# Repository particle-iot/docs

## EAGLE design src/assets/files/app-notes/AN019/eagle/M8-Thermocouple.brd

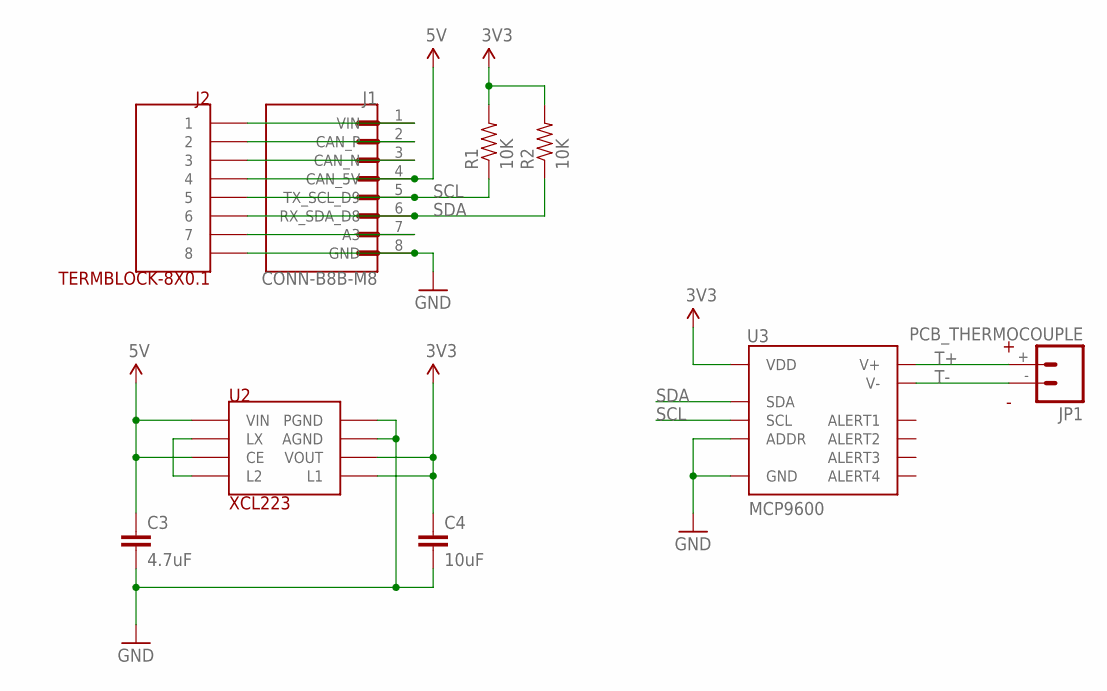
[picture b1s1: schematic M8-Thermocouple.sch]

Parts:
C3: 4.7uF; 0603-CAP
C4: 10uF; 0603-CAP
J1: CONN-B8B-M8; JST_B8B-PH-SM4-TB(LF)(SN)
J2: TERMBLOCK-8X0.1
JP1: PCB_THERMOCOUPLE; PCC-SMP
R1, R2: 10K; 0603-RES
U2: XCL223; REG-XCL223-LESS-CREAM
U3: MCP9600; MQFN-20

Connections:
3V3: C4.1, R1.2, R2.2, U2.3 (VOUT), U2.7 (L1), U3.8 (VDD)
5V: C3.1, J1.4 (CAN_5V), J2.P$4 (4), U2.4 (CE), U2.6 (VIN)
A3: J1.7 (A3), J2.P$7 (7)
CAN_N: J1.3 (CAN_N), J2.P$3 (3)
CAN_P: J1.2 (CAN_P), J2.P$2 (2)
GND: C3.2, C4.2, J1.8 (GND), J2.P$8 (8), U2.1 (PGND), U2.2 (AGND), U3.1 (GND), U3.3 (GND), U3.5 (GND), U3.6 (GND), U3.7 (GND), U3.9 (GND), U3.10 (GND), U3.13 (GND), U3.16 (ADDR), U3.17 (GND), U3.18 (GND), U3.21 (GND)
LX: U2.5 (LX), U2.8 (L2)
SCL: J1.5 (TX_SCL_D9), J2.P$5 (5), R1.1, U3.19 (SCL)
SDA: J1.6 (RX_SDA_D8), J2.P$6 (6), R2.1, U3.20 (SDA)
T+: JP1.+, U3.2 (V+)
T-: JP1.-, U3.4 (V-)
VIN: J1.1 (VIN), J2.P$1 (1)

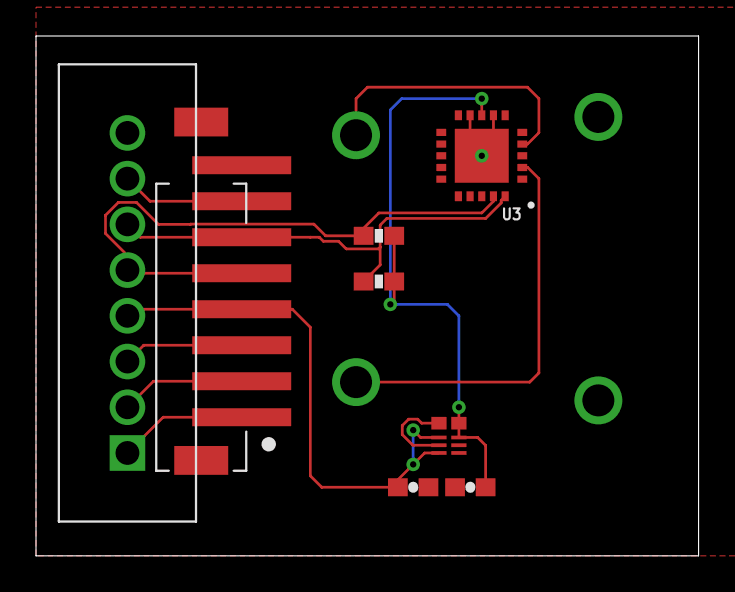
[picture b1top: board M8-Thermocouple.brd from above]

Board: 2 copper layers, 36.8 x 28.9 mm, 9 parts (1 on the bottom side), 12 nets.

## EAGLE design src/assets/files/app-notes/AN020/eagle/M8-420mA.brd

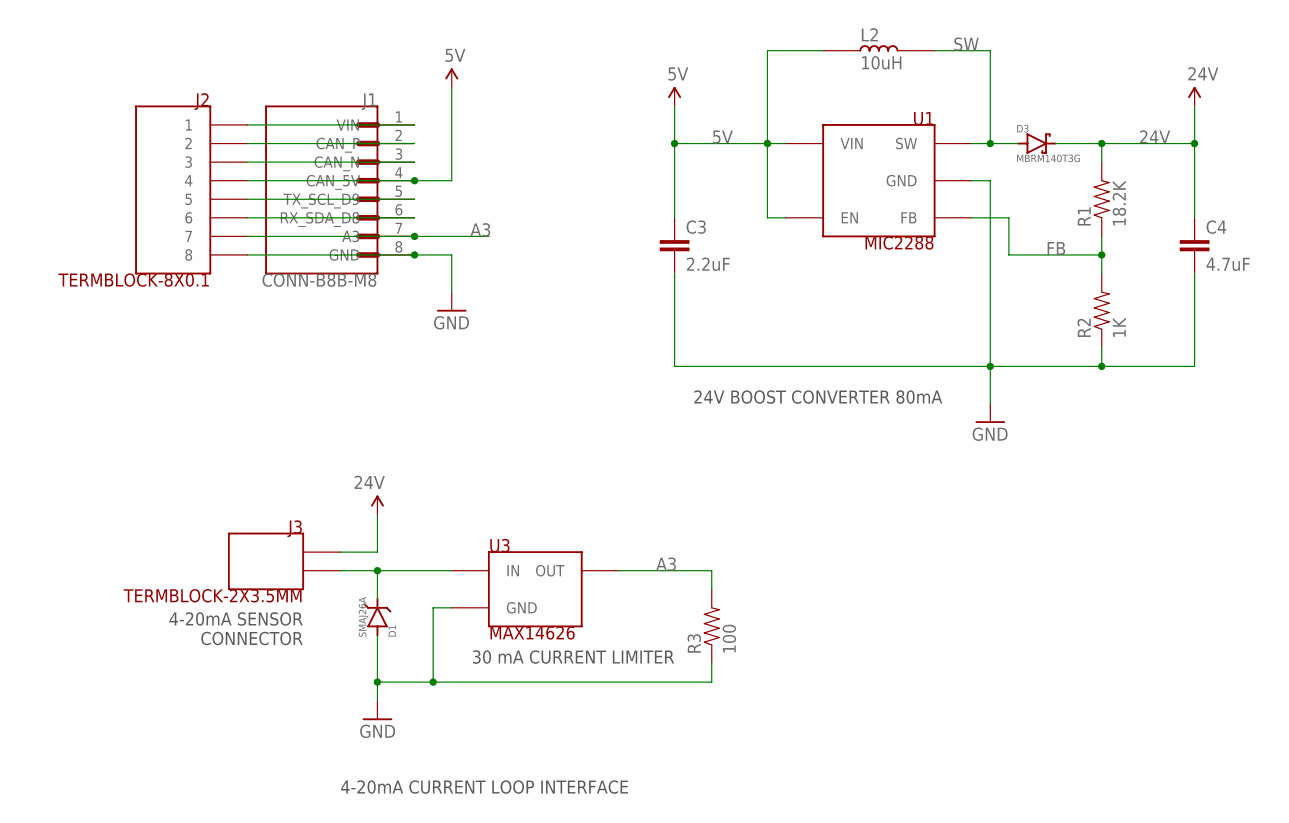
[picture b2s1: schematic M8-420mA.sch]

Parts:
C3: 2.2uF; 0603-CAP
C4: 4.7uF; 0805
D1: SMAJ26A; DO-214AC-LITTELFUSE
D3: MBRM140T3G
J1: CONN-B8B-M8; JST_B8B-PH-SM4-TB(LF)(SN)
J2: TERMBLOCK-8X0.1
J3: TERMBLOCK-2X3.5MM
L2: 10uH; BOURNS-INDUCTOR-3X3
R1: 18.2K; 0603-RES
R2: 1K; 0603-RES
R3: 100; 0603-RES
U1: MIC2288; TSOT23-5-MICROCHIP
U3: MAX14626; 6-TDFN-MAXIM

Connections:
5V: C3.1, J1.4 (CAN_5V), J2.P$4 (4), L2.1, U1.4 (EN), U1.5 (VIN)
24V: C4.1, D3.1 (CATHODE), J3.1, R1.2
A3: J1.7 (A3), J2.P$7 (7), R3.2, U3.6 (OUT)
CAN_N: J1.3 (CAN_N), J2.P$3 (3)
CAN_P: J1.2 (CAN_P), J2.P$2 (2)
FB: R1.1, R2.2, U1.3 (FB)
GND: C3.2, C4.2, D1.A (ANODE), J1.8 (GND), J2.P$8 (8), R2.1, R3.1, U1.2 (GND), U3.2 (GND), U3.3 (GND), U3.4 (GND), U3.5 (GND), U3.EP (GND)
unnamed: J1.5 (TX_SCL_D9), J2.P$5 (5)
SDA: J1.6 (RX_SDA_D8), J2.P$6 (6)
SEN1: D1.C (CATHODE), J3.2, U3.1 (IN)
SW: D3.2 (ANODE), L2.2, U1.1 (SW)
VIN: J1.1 (VIN), J2.P$1 (1)

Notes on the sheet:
24V BOOST CONVERTER 80mA
30 mA CURRENT LIMITER
4-20mA SENSOR CONNECTOR
4-20mA CURRENT LOOP INTERFACE

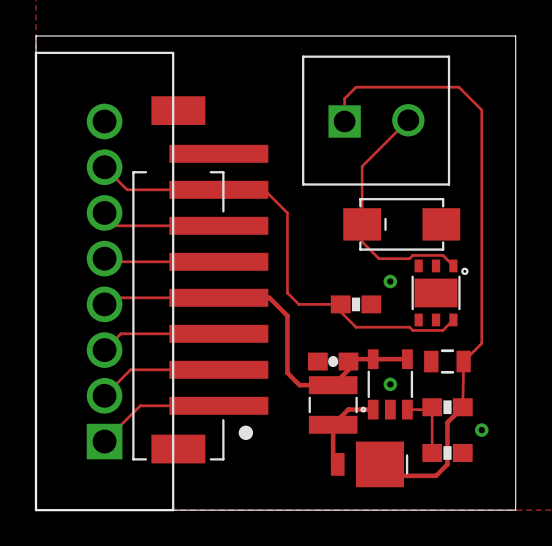
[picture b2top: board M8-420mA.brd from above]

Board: 2 copper layers, 26.6 x 26.3 mm, 13 parts (0 on the bottom side), 12 nets.

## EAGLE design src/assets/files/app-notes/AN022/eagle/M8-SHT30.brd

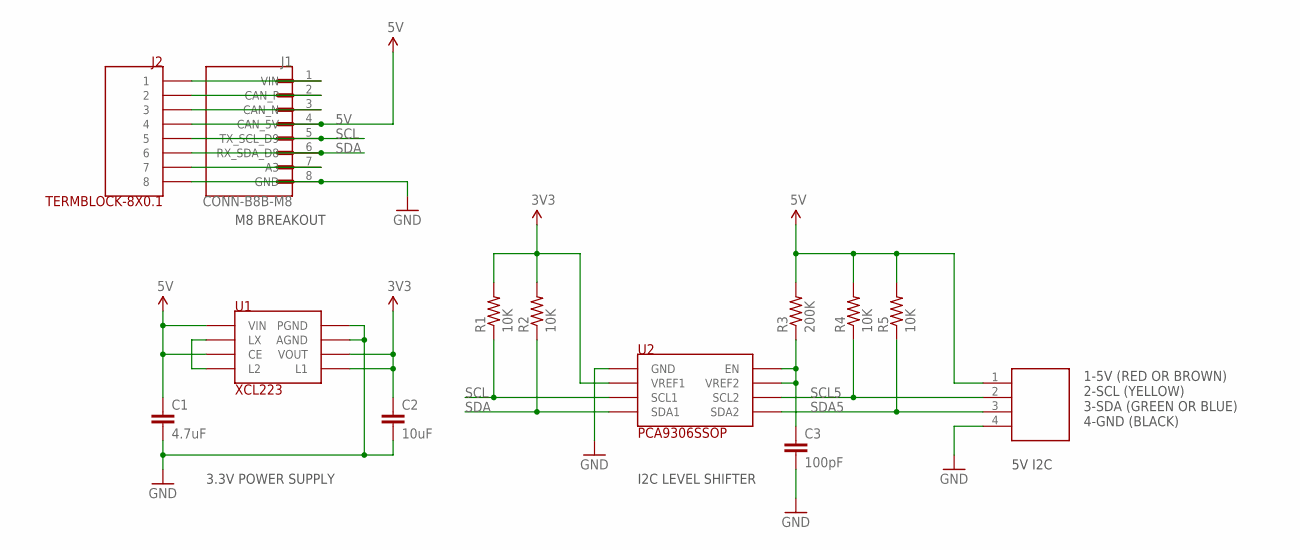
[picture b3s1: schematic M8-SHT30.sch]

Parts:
C1: 4.7uF; 0603-CAP
C2: 10uF; 0603-CAP
C3: 100pF; 0603-CAP
J1: CONN-B8B-M8; JST_B8B-PH-SM4-TB(LF)(SN)
J2: TERMBLOCK-8X0.1
R1, R2, R4, R5: 10K; 0603-RES
R3: 200K; 0603-RES
U1: XCL223; REG-XCL223-LESS-CREAM
U2: PCA9306SSOP; 8-SSOP-TI
U$1: TERMBLOCK-4X0.15

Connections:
3V3: C2.1, R1.2, R2.2, U1.3 (VOUT), U1.7 (L1), U2.2 (VREF1)
5V: C1.1, J1.4 (CAN_5V), J2.P$4 (4), R3.2, R4.2, R5.2, U1.4 (CE), U1.6 (VIN), U$1.1
A3: J1.7 (A3), J2.P$7 (7)
CAN_N: J1.3 (CAN_N), J2.P$3 (3)
CAN_P: J1.2 (CAN_P), J2.P$2 (2)
GND: C1.2, C2.2, C3.2, J1.8 (GND), J2.P$8 (8), U1.1 (PGND), U1.2 (AGND), U2.1 (GND), U$1.4
LX: U1.5 (LX), U1.8 (L2)
SCL: J1.5 (TX_SCL_D9), J2.P$5 (5), R1.1, U2.3 (SCL1)
SCL5: R4.1, U2.6 (SCL2), U$1.2
SDA: J1.6 (RX_SDA_D8), J2.P$6 (6), R2.1, U2.4 (SDA1)
SDA5: R5.1, U2.5 (SDA2), U$1.3
VIN: J1.1 (VIN), J2.P$1 (1)
VREF2_EN: C3.1, R3.1, U2.7 (VREF2), U2.8 (EN)

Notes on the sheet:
3.3V POWER SUPPLY
M8 BREAKOUT
I2C LEVEL SHIFTER
5V I2C
1-5V (RED OR BROWN) 2-SCL (YELLOW) 3-SDA (GREEN OR BLUE) 4-GND (BLACK)

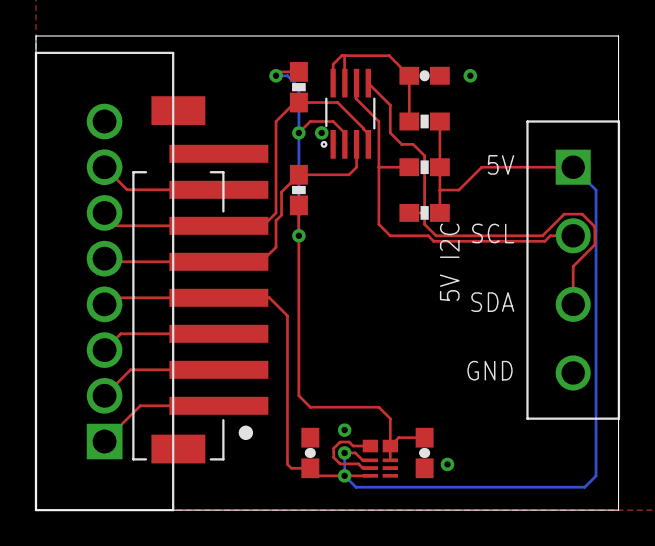
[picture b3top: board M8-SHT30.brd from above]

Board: 2 copper layers, 32.4 x 26.3 mm, 13 parts (0 on the bottom side), 13 nets.

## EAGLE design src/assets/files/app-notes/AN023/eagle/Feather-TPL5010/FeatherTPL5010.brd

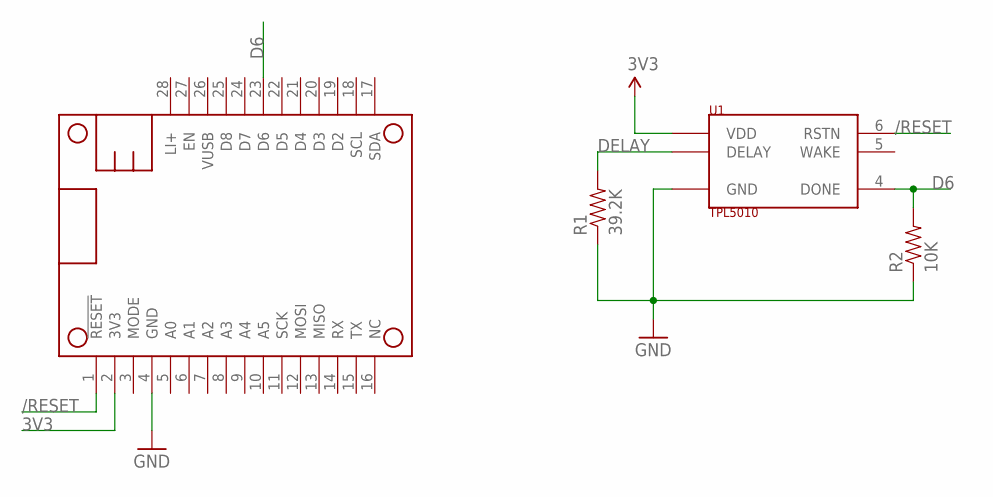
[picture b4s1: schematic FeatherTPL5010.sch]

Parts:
MS1: FEATHERWING_NODIM
R1: 39.2K; 0603-RES
R2: 10K; 0603-RES
U1: TPL5010; SOT-23-6-TI

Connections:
3V3: MS1.2 (3V3), U1.1 (VDD)
/RESET: MS1.1 (!RESET), U1.6 (RSTN)
D6: MS1.23 (D6), R2.2, U1.4 (DONE)
DELAY: R1.2, U1.3 (DELAY)
GND: MS1.4 (GND), R1.1, R2.1, U1.2 (GND)

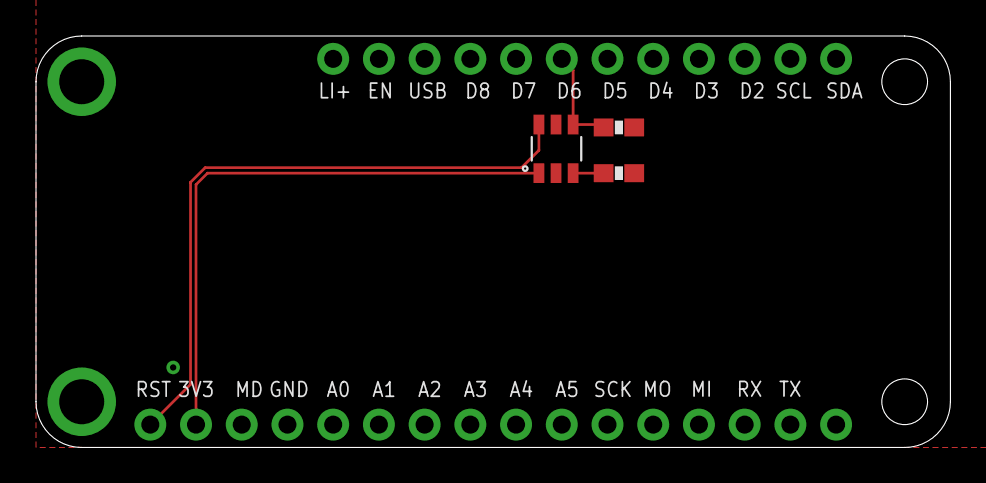
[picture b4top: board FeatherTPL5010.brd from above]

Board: 2 copper layers, 50.8 x 22.9 mm, 4 parts (0 on the bottom side), 5 nets.

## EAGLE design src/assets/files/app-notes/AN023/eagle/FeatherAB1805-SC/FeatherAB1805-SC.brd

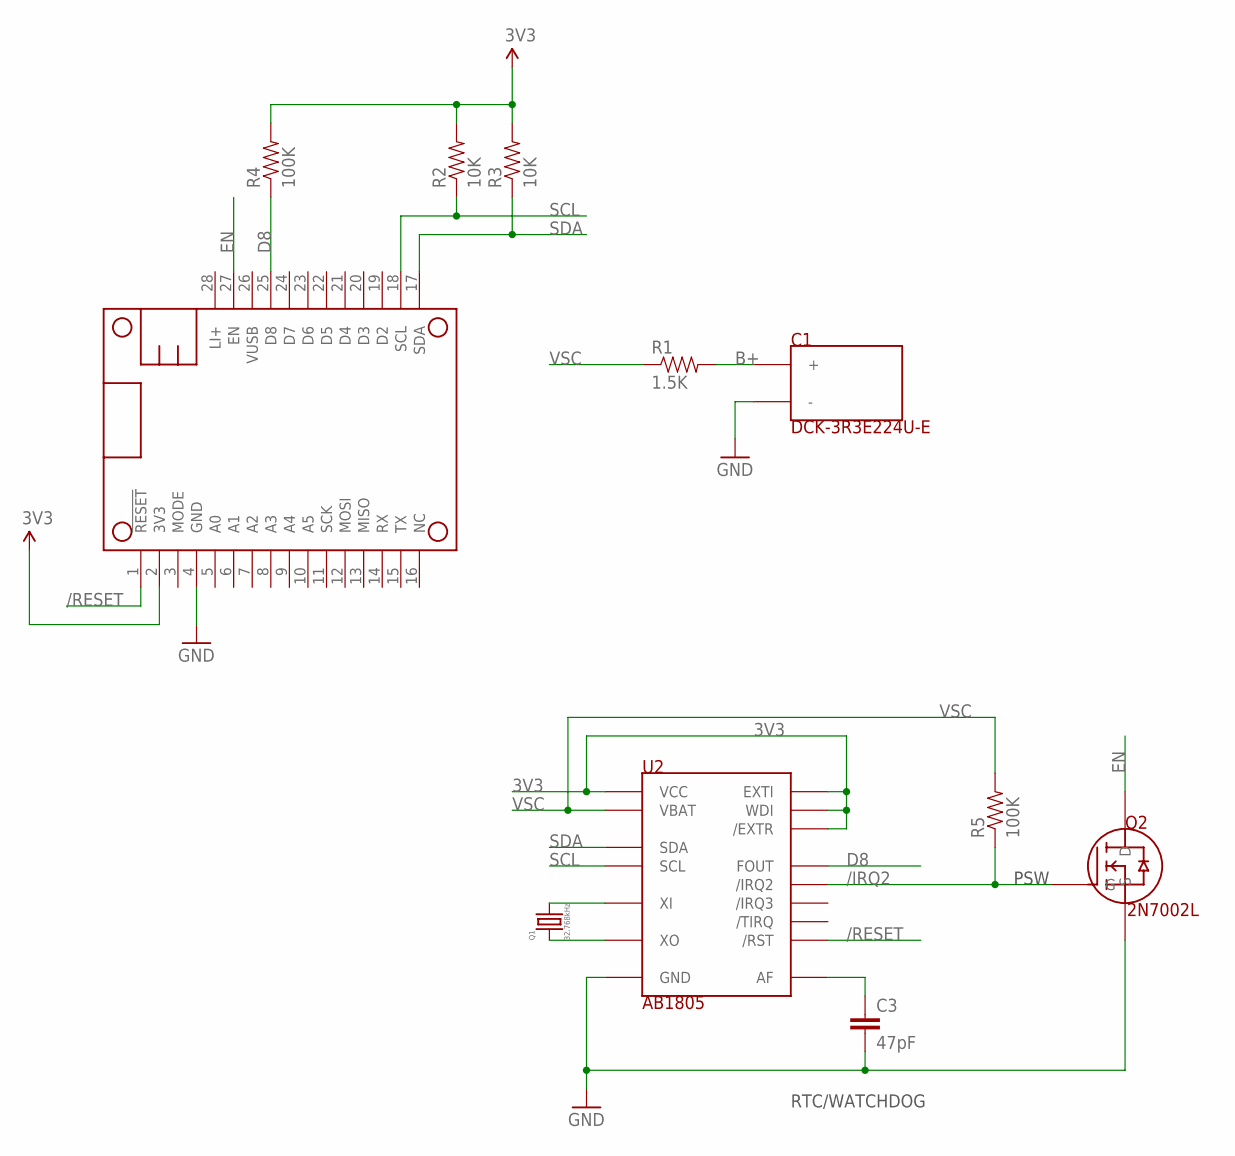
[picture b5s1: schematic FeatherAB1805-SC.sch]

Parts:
C1: DCK-3R3E224U-E; SUPERCAP-DCK-3R3E224U-E
C3: 47pF; 0603-CAP
MS1: FEATHERWING_NODIM
Q1: 32.768kHz; ABS07-120-CRYSTAL
Q2: 2N7002L
R1: 1.5K; 0603-RES
R2, R3: 10K; 0603-RES
R4, R5: 100K; 0603-RES
U2: AB1805; 16-VFQFN-ABRACON

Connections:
3V3: MS1.2 (3V3), R2.2, R3.2, R4.2, U2.2 (WDI), U2.3 (/EXTR), U2.10 (EXTI), U2.13 (VCC)
/IRQ2: Q2.1 (G), R5.1, U2.4 (/IRQ2)
/RESET: MS1.1 (!RESET), U2.1 (/RST)
AF: C3.1, U2.14 (AF)
B+: C1.+, R1.2
D8: MS1.25 (D8), R4.1, U2.11 (FOUT)
EN: MS1.27 (EN), Q2.3 (D)
GND: C1.-, C3.2, MS1.4 (GND), Q2.2 (S), U2.9 (GND), U2.EP (GND)
SCL: MS1.18 (SCL), R2.1, U2.7 (SCL)
SDA: MS1.17 (SDA), R3.1, U2.6 (SDA)
VSC: R1.1, R5.2, U2.5 (VBAT)
XI: Q1.2, U2.16 (XI)
XO: Q1.1, U2.15 (XO)

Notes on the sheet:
PSW
RTC/WATCHDOG

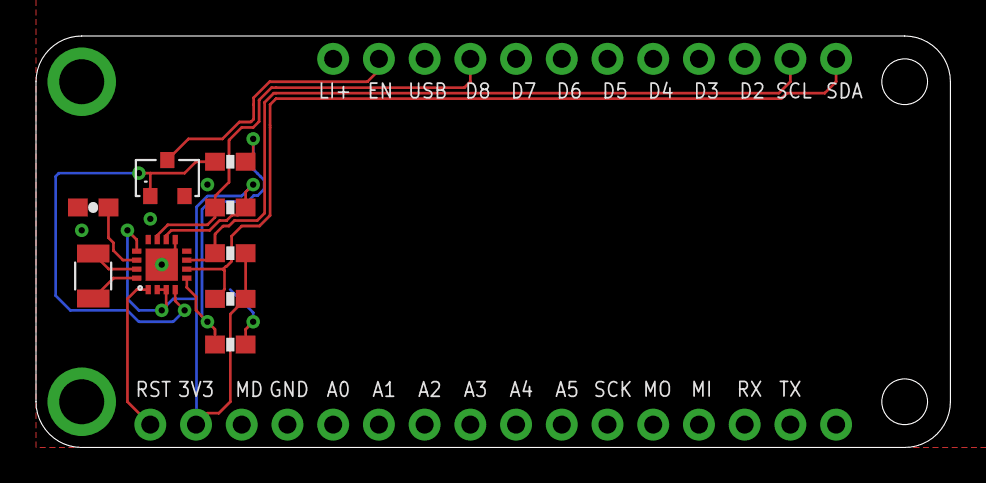
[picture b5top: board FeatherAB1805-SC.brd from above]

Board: 2 copper layers, 50.8 x 22.9 mm, 11 parts (1 on the bottom side), 13 nets.

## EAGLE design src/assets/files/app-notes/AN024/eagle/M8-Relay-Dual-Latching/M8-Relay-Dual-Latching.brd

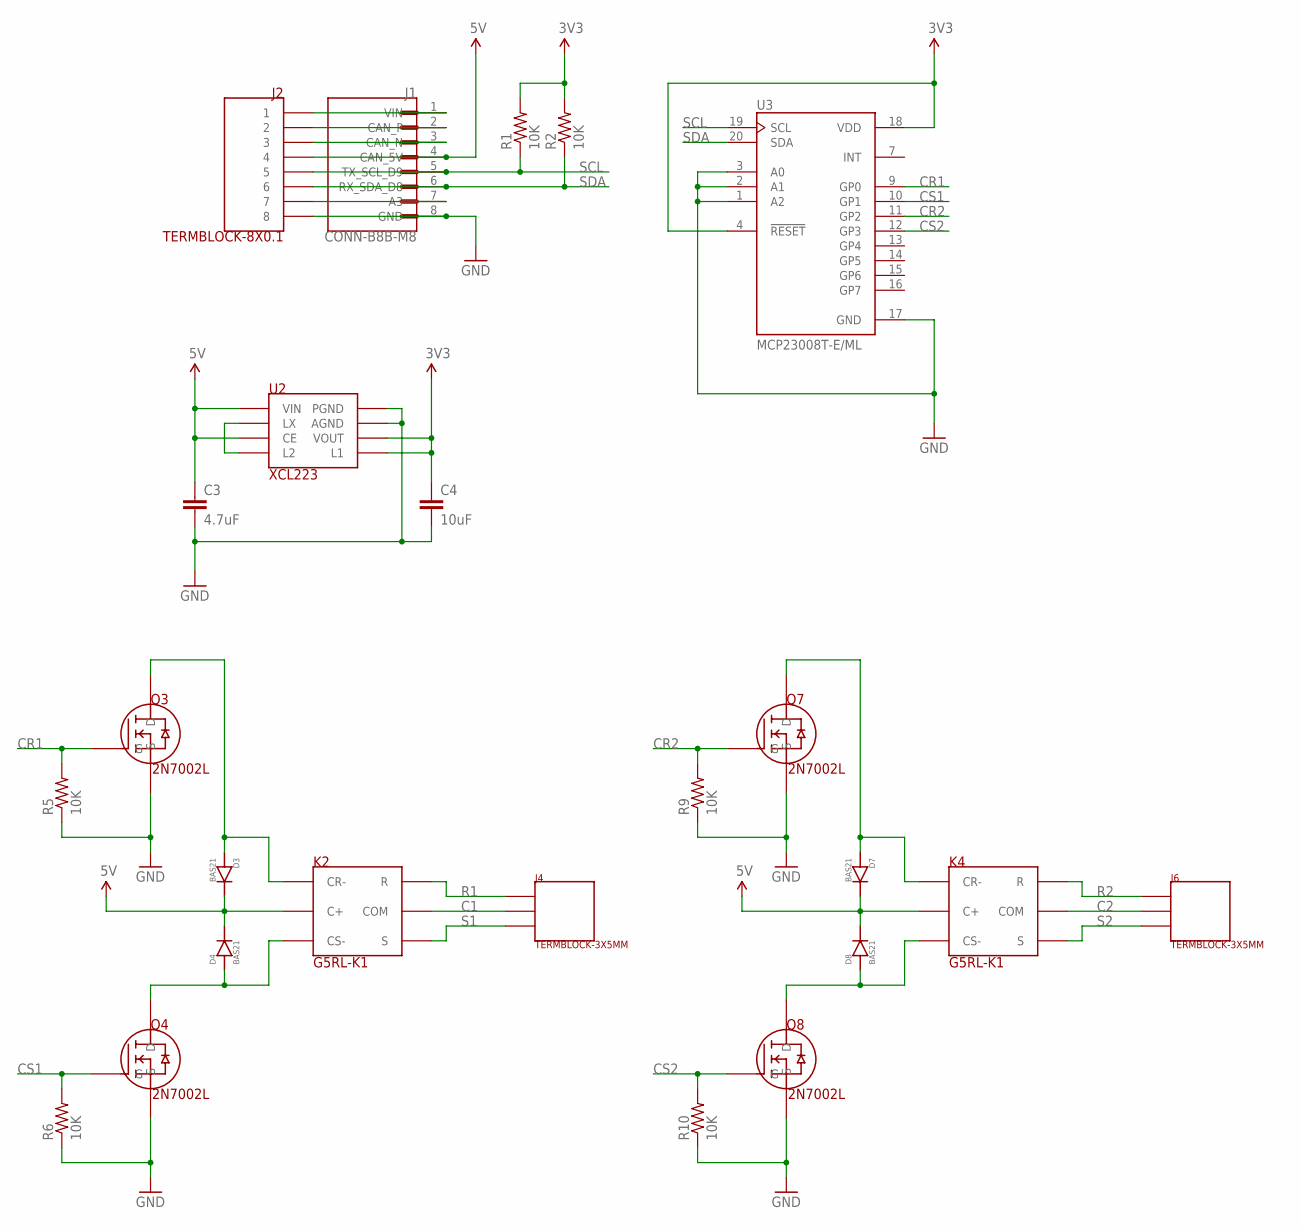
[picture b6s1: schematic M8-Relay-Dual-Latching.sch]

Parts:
C3: 4.7uF; 0603-CAP
C4: 10uF; 0603-CAP
D3, D4, D7, D8: BAS21; DIODE-BAS21
J1: CONN-B8B-M8; JST_B8B-PH-SM4-TB(LF)(SN)
J2: TERMBLOCK-8X0.1
J4, J6: TERMBLOCK-3X5MM
K2, K4: G5RL-K1; RELAY-G5RL-K1-E-LATCHING-SPDT
Q3, Q4, Q7, Q8: 2N7002L
R1, R2, R5, R6, R9, R10: 10K; 0603-RES
U2: XCL223; REG-XCL223-LESS-CREAM
U3: MCP23008T-E/ML; QFN21P50_400X400X100L40X24T270N

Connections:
3V3: C4.1, R1.2, R2.2, U2.3 (VOUT), U2.7 (L1), U3.4 (!RESET), U3.18 (VDD)
5V: C3.1, D3.3 (CATHODE), D4.3 (CATHODE), D7.3 (CATHODE), D8.3 (CATHODE), J1.4 (CAN_5V), J2.P$4 (4), K2.9 (C+), K4.9 (C+), U2.4 (CE), U2.6 (VIN)
A3: J1.7 (A3), J2.P$7 (7)
C1: J4.2, K2.3 (COM), K2.6 (COM)
C2: J6.2, K4.3 (COM), K4.6 (COM)
CAN_N: J1.3 (CAN_N), J2.P$3 (3)
CAN_P: J1.2 (CAN_P), J2.P$2 (2)
CR1: Q3.1 (G), R5.2, U3.9 (GP0)
CR1-1: D3.1 (ANODE), K2.1 (CR-), Q3.3 (D)
CR2: Q7.1 (G), R9.2, U3.11 (GP2)
CR2-: D7.1 (ANODE), K4.1 (CR-), Q7.3 (D)
CS1: Q4.1 (G), R6.2, U3.10 (GP1)
CS1-1: D4.1 (ANODE), K2.8 (CS-), Q4.3 (D)
CS2: Q8.1 (G), R10.2, U3.12 (GP3)
CS2-: D8.1 (ANODE), K4.8 (CS-), Q8.3 (D)
GND: C3.2, C4.2, J1.8 (GND), J2.P$8 (8), Q3.2 (S), Q4.2 (S), Q7.2 (S), Q8.2 (S), R5.1, R6.1, R9.1, R10.1, U2.1 (PGND), U2.2 (AGND), U3.1 (A2), U3.2 (A1), U3.3 (A0), U3.17 (GND)
LX: U2.5 (LX), U2.8 (L2)
R1: J4.1, K2.2 (R), K2.7 (R)
R2: J6.1, K4.2 (R), K4.7 (R)
S1: J4.3, K2.4 (S), K2.5 (S)
S2: J6.3, K4.4 (S), K4.5 (S)
SCL: J1.5 (TX_SCL_D9), J2.P$5 (5), R1.1, U3.19 (SCL)
SDA: J1.6 (RX_SDA_D8), J2.P$6 (6), R2.1, U3.20 (SDA)
VIN: J1.1 (VIN), J2.P$1 (1)

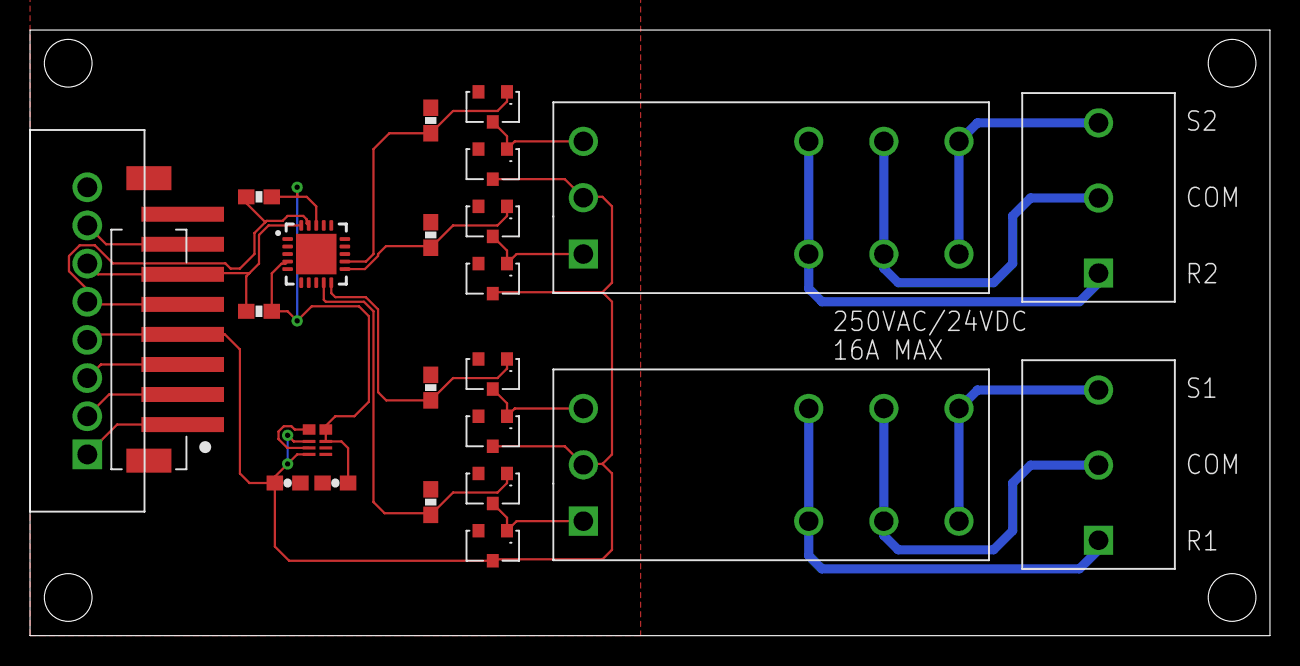
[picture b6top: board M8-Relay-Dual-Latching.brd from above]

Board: 2 copper layers, 82.5 x 40.3 mm, 24 parts (0 on the bottom side), 24 nets.

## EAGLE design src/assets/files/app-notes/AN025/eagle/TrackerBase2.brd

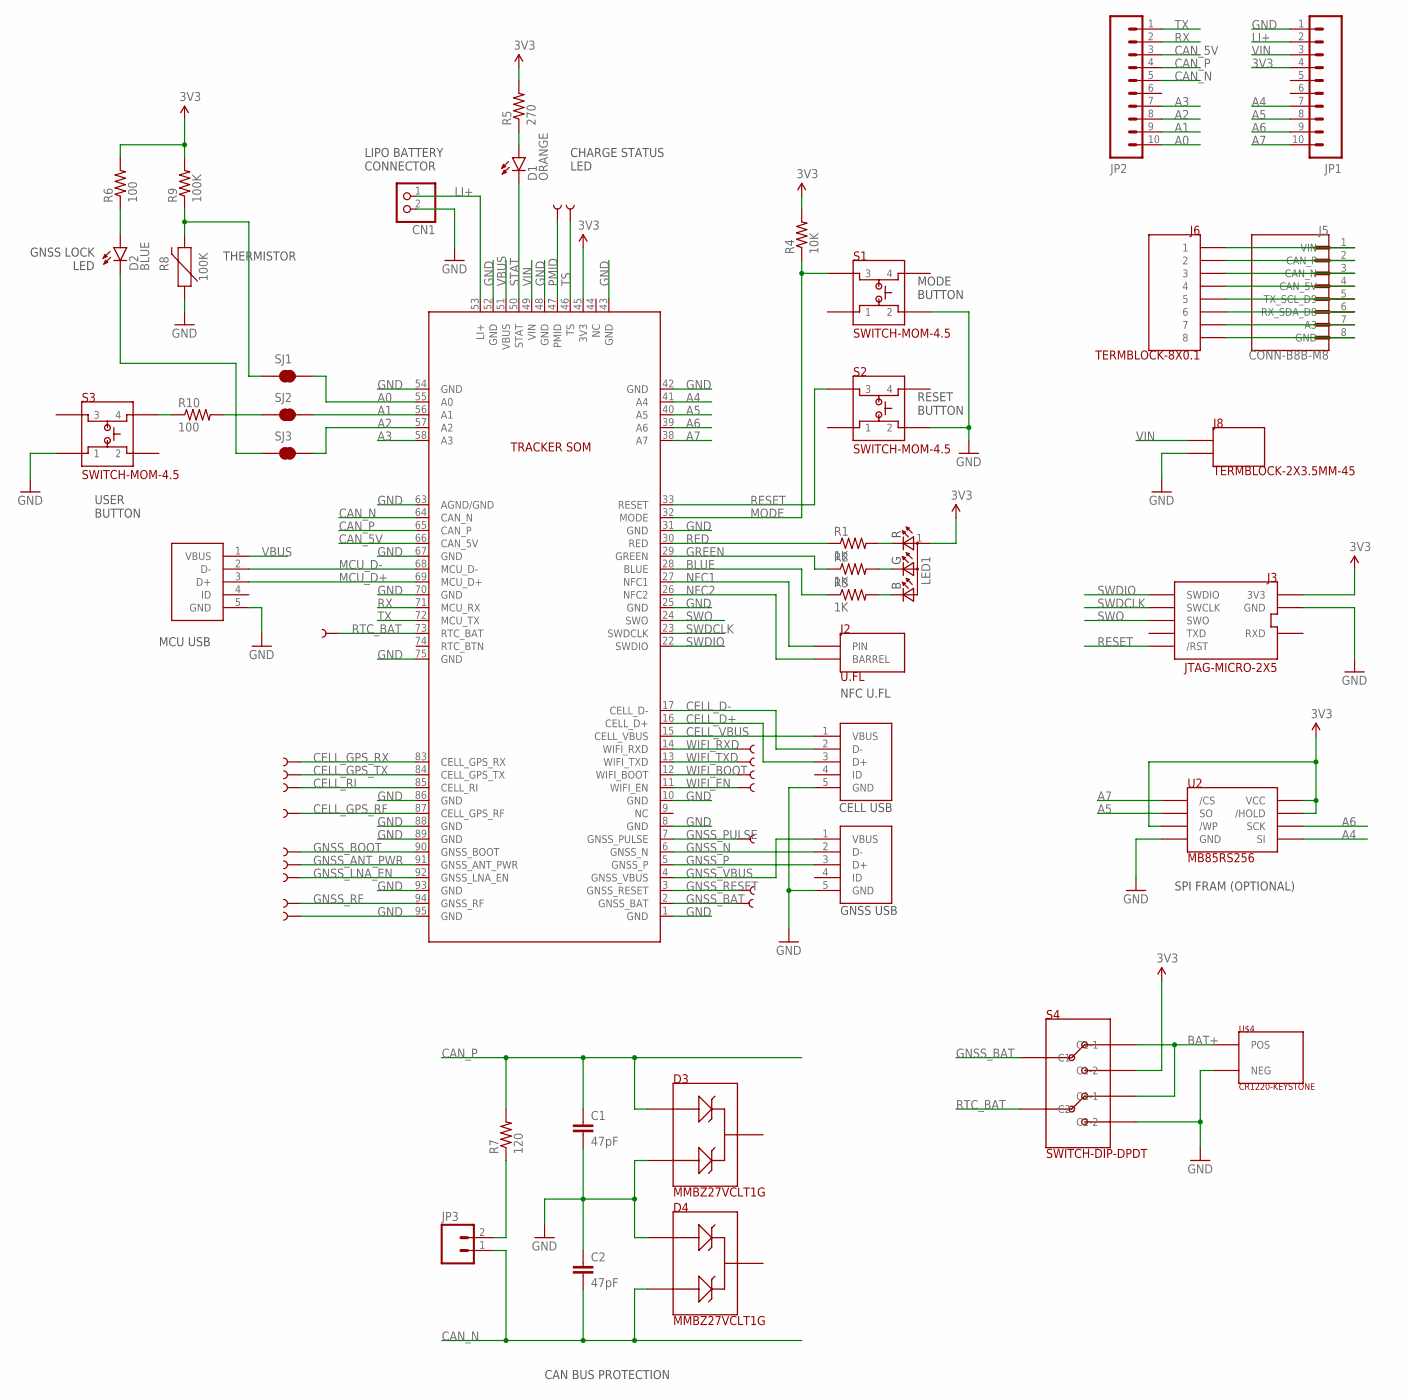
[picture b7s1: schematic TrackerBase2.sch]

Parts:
C1, C2: 47pF; 0603-CAP
CN1: JST_2PIN-THM; JST-PH-2-THM
D1: ORANGE; LED-0603
D2: BLUE; LED-0603
D3, D4: MMBZ27VCLT1G; SOT-23-3-ON
J1, J4, J7: USB-MICRO-B-VERT-PTH
J2: U.FL; CONN-UFL-TE
J3: JTAG-MICRO-2X5
J5: CONN-B8B-M8; JST_B8B-PH-SM4-TB(LF)(SN)
J6: TERMBLOCK-8X0.1
J8: TERMBLOCK-2X3.5MM-45
JP1, JP2: M10; 1X10
JP3: M02PTH; 1X02
LED1: RGB; LED-RGB-CREE-SMD
R1, R2, R3: 1K; 0603-RES
R4: 10K; 0603-RES
R5: 270; 0603-RES
R6, R10: 100; 0603-RES
R7: 120; 0603-RES
R8: 100K; 0603
R9: 100K; 0603-RES
S1, S2, S3: SWITCH-MOM-4.5
S4: SWITCH-DIP-DPDT
SJ1, SJ2, SJ3: JUMPER-PAD-2-NC_BY_TRACENO_SILK; PAD-JUMPER-2-NC_BY_TRACE_NO_SILK
TP1, TP2, TP3, TP4, TP5, TP6, TP7, TP8, TP9, TP10, TP11, TP12, TP13, TP14, TP15, TP16, TP17, TP18, TP19: TEST-POINTTP_15TH_THRU; TP_15TH
U1: TRACKER-SOM-SKIP-NC
U2: MB85RS256; 8-SOIC-MAXIM
U$4: CR1220-KEYSTONE

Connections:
3V3: J3.1 (3V3), JP1.4, LED1.1 (A), R4.2, R5.2, R6.2, R9.2, S4.C1-2, U1.45 (3V3), U2.3 (/WP), U2.7 (/HOLD), U2.8 (VCC)
A0: JP2.10, SJ1.2, U1.55 (A0)
A1: JP2.9, SJ2.2, U1.56 (A1)
A2: JP2.8, SJ3.2, U1.57 (A2)
A3: J5.7 (A3), J6.P$7 (7), JP2.7, U1.58 (A3)
A4: JP1.7, U1.41 (A4), U2.5 (SI)
A5: JP1.8, U1.40 (A5), U2.2 (SO)
A6: JP1.9, U1.39 (A6), U2.6 (SCK)
A7: JP1.10, U1.38 (A7), U2.1 (/CS)
BAT+: S4.C1-1, S4.C2-1, U$4.POS
BLUE: R3.1, U1.28 (BLUE)
CAN_5V: J5.4 (CAN_5V), J6.P$4 (4), JP2.3, U1.66 (CAN_5V)
CAN_N: C2.2, D4.2, J5.3 (CAN_N), J6.P$3 (3), JP2.5, JP3.1, U1.64 (CAN_N)
CAN_P: C1.1, D3.1, J5.2 (CAN_P), J6.P$2 (2), JP2.4, R7.2, U1.65 (CAN_P)
CELL_D+: J1.3 (D+), U1.16 (CELL_D+)
CELL_D-: J1.2 (D-), U1.17 (CELL_D-)
CELL_GPS_RF: TP14.P$1, U1.87 (CELL_GPS_RF)
CELL_GPS_RX: TP7.P$1, U1.83 (CELL_GPS_RX)
CELL_GPS_TX: TP8.P$1, U1.84 (CELL_GPS_TX)
CELL_RI: TP9.P$1, U1.85 (CELL_RI)
CELL_VBUS: J1.1 (VBUS), U1.15 (CELL_VBUS)
GND: C1.2, C2.1, CN1.2 (1), D3.2, D4.1, J1.5 (GND), J3.3 (GND), J3.5 (GND), J3.9 (GND), J4.5 (GND), J5.8 (GND), J6.P$8 (8), J7.5 (GND), J8.2, JP1.1, R8.1, S1.2, S2.2, S3.1, S4.C2-2, TP19.P$1, U1.1 (GND), U1.8 (GND), U1.10 (GND), U1.25 (GND), U1.31 (GND), U1.42 (GND), U1.43 (GND), U1.48 (GND), U1.52 (GND), U1.54 (GND), U1.63 (AGND/GND), U1.67 (GND), U1.70 (GND), U1.75 (GND), U1.86 (GND), U1.88 (GND), U1.89 (GND), U1.93 (GND), U1.95 (GND), U2.4 (GND), U$4.NEG
GNSS_ANT_PWR: TP11.P$1, U1.91 (GNSS_ANT_PWR)
GNSS_BAT: S4.C1, TP17.P$1, U1.2 (GNSS_BAT)
GNSS_BOOT: TP10.P$1, U1.90 (GNSS_BOOT)
GNSS_LNA_EN: TP12.P$1, U1.92 (GNSS_LNA_EN)
GNSS_N: J4.2 (D-), U1.6 (GNSS_N)
GNSS_P: J4.3 (D+), U1.5 (GNSS_P)
GNSS_PULSE: TP5.P$1, U1.7 (GNSS_PULSE)
GNSS_RESET: TP6.P$1, U1.3 (GNSS_RESET)
GNSS_RF: TP13.P$1, U1.94 (GNSS_RF)
GNSS_VBUS: J4.1 (VBUS), U1.4 (GNSS_VBUS)
GREEN: R2.1, U1.29 (GREEN)
LI+: CN1.1 (2), JP1.2, U1.53 (LI+)
MCU_D+: J7.3 (D+), U1.69 (MCU_D+)
MCU_D-: J7.2 (D-), U1.68 (MCU_D-)
MODE: R4.1, S1.3, U1.32 (MODE)
unnamed: JP3.2, R7.1
unnamed: LED1.2 (B), R3.2
unnamed: LED1.3 (G), R2.2
unnamed: LED1.4 (R), R1.2
unnamed: D1.A, R5.1
unnamed: R8.2, R9.1, SJ1.1
unnamed: D2.A, R6.1
unnamed: R10.1, S3.4
unnamed: R10.2, SJ2.1
unnamed: D2.C, SJ3.1
NFC1: J2.PIN, U1.27 (NFC1)
NFC2: J2.BL (BARREL), J2.BR (BARREL), U1.26 (NFC2)
PMID: TP15.P$1, U1.47 (PMID)
RED: R1.1, U1.30 (RED)
RESET: J3.10 (/RST), S2.3, U1.33 (RESET)
RTC_BAT: S4.C2, TP18.P$1, U1.73 (RTC_BAT)
RX: J5.6 (RX_SDA_D8), J6.P$6 (6), JP2.2, U1.71 (MCU_RX)
STAT: D1.C, U1.50 (STAT)
SWDCLK: J3.4 (SWCLK), U1.23 (SWDCLK)
SWDIO: J3.2 (SWDIO), U1.22 (SWDIO)
SWO: J3.6 (SWO), U1.24 (SWO)
TS: TP16.P$1, U1.46 (TS)
TX: J5.5 (TX_SCL_D9), J6.P$5 (5), JP2.1, U1.72 (MCU_TX)
VBUS: J7.1 (VBUS), U1.51 (VBUS)
VIN: J5.1 (VIN), J6.P$1 (1), J8.1, JP1.3, U1.49 (VIN)
WIFI_BOOT: TP3.P$1, U1.12 (WIFI_BOOT)
WIFI_EN: TP4.P$1, U1.11 (WIFI_EN)
WIFI_RXD: TP1.P$1, U1.14 (WIFI_RXD)
WIFI_TXD: TP2.P$1, U1.13 (WIFI_TXD)

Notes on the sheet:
NFC U.FL
RESET BUTTON
MODE BUTTON
CHARGE STATUS LED
GNSS LOCK LED
THERMISTOR
USER BUTTON
LIPO BATTERY CONNECTOR
SPI FRAM (OPTIONAL)
CAN BUS PROTECTION
MCU USB
GNSS USB
CELL USB

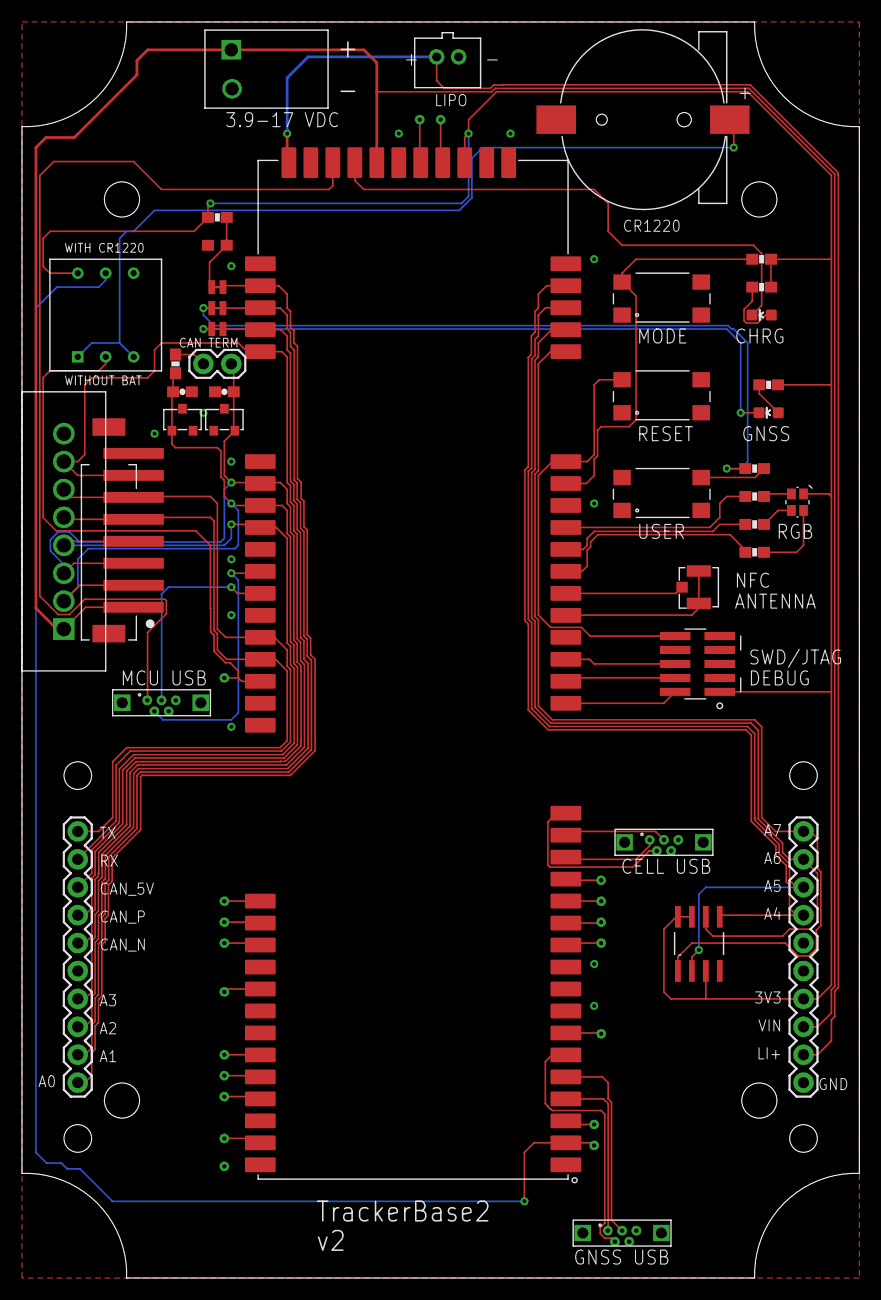
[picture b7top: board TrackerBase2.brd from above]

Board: 2 copper layers, 76.2 x 114.3 mm, 58 parts (0 on the bottom side), 66 nets.

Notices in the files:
parts and their libraries:
SparkFun-Electromechanical: Licensing: Creative Commons ShareAlike 4.0 International - https://creativecommons.org/licenses/by-sa/4.0
